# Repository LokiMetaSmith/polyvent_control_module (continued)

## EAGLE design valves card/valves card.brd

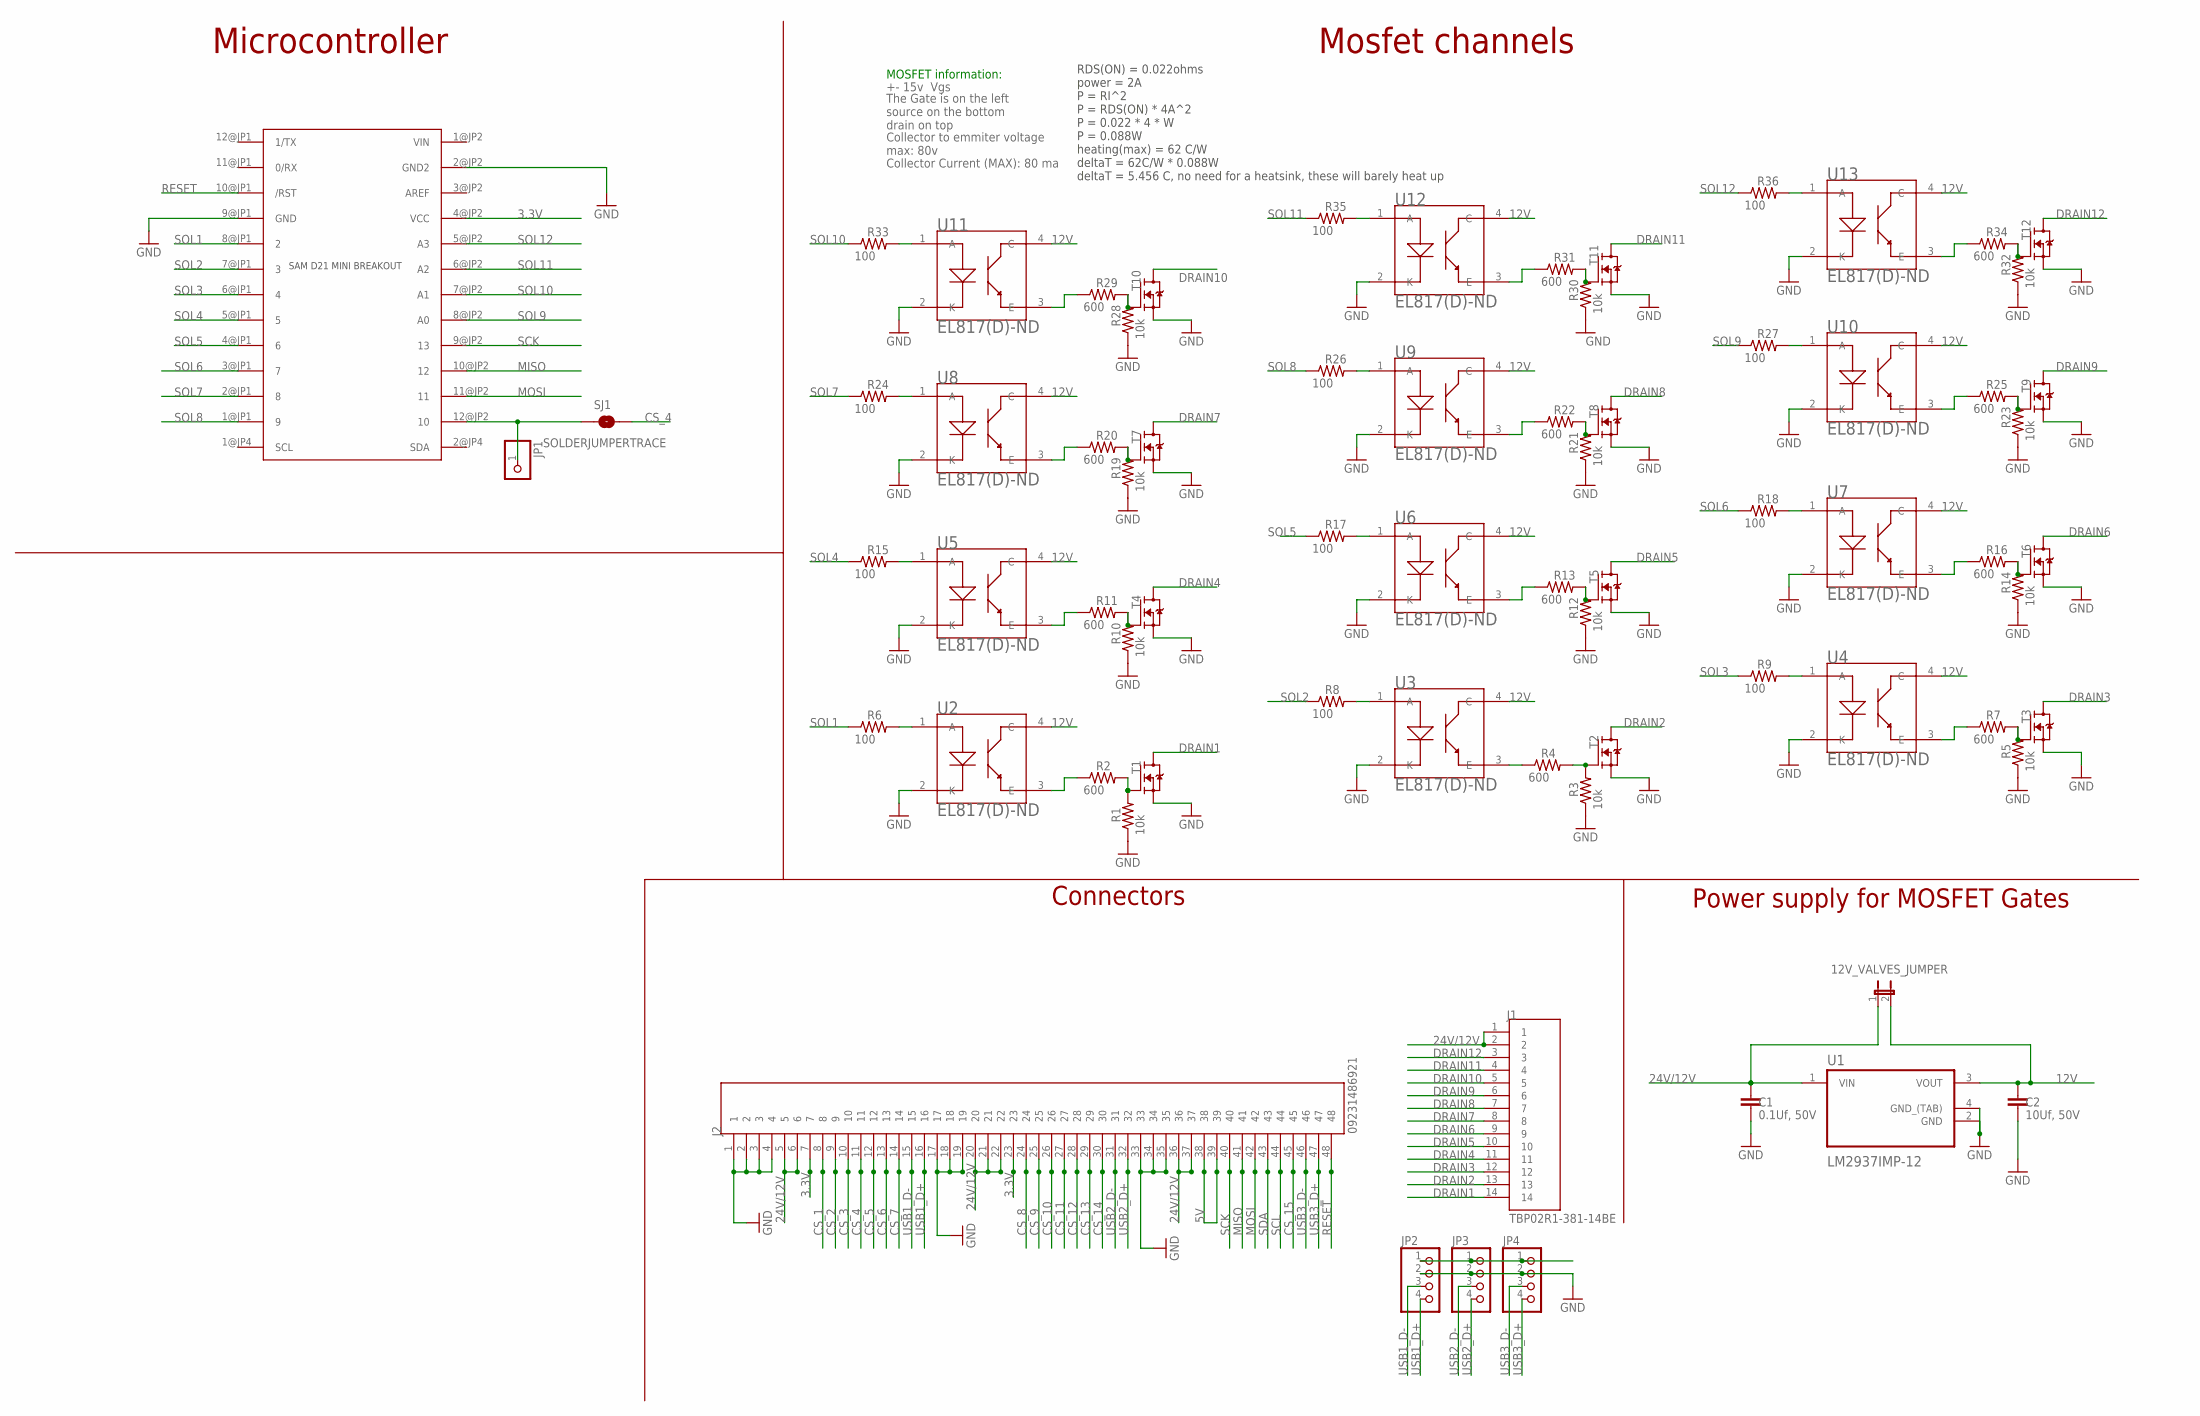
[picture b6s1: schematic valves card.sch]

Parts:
12V_VALVES_JUMPER: JUMPER-2SMD-NO; SJ_2S-NO
C1: 0.1Uf, 50V; 0805
C2: 10Uf, 50V; 0805
J1: TBP02R1-381-14BE; CUI_TBP02R1-381-14BE
J2: 09231486921; HARTING_09231486921
JP1: PINHD-1X1; 1X01
JP2, JP3, JP4: PINHD-1X4; 1X04
M2: SAM_D21_MINI_BREAKOUT; JP1_SPARKFUN-SAMD21-MINI-BREAKOUT-V10
R1, R3, R5, R10, R12, R14, R19, R21, R23, R28, R30, R32: 10k; 0805
R2, R4, R7, R11, R13, R16, R20, R22, R25, R29, R31, R34: 600; 0805
R6, R8, R9, R15, R17, R18, R24, R26, R27, R33, R35, R36: 100; 0805
SJ1: SOLDERJUMPERTRACE; SJ_2S-TRACE
T1, T2, T3, T4, T5, T6, T7, T8, T9, T10, T11, T12: IRLZ44NSTRLPBF; DPAK_TO252
U1: LM2937IMP-12; SOT230P700X180-4N
U2, U3, U4, U5, U6, U7, U8, U9, U10, U11, U12, U13: EL817(D)-ND; DIP4

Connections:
3.3V: J2.7, J2.23, M2.4@JP2 (VCC)
5V: J2.38, J2.39, JP2.1, JP3.1, JP4.1
12V: 12V_VALVES_JUMPER.2, C2.1, U1.3 (VOUT), U2.4 (C), U3.4 (C), U4.4 (C), U5.4 (C), U6.4 (C), U7.4 (C), U8.4 (C), U9.4 (C), U10.4 (C), U11.4 (C), U12.4 (C), U13.4 (C)
24V/12V: 12V_VALVES_JUMPER.1, C1.1, J1.1, J1.2, J2.5, J2.6, J2.20, J2.21, J2.22, J2.36, J2.37, U1.1 (VIN)
AREF: M2.3@JP2 (AREF)
CS_1: J2.8
CS_2: J2.9
CS_3: J2.10
CS_4: J2.11, SJ1.2
CS_5: J2.12
CS_6: J2.13
CS_7: J2.14
CS_8: J2.24
CS_9: J2.25
CS_10: J2.26
CS_11: J2.27
CS_12: J2.28
CS_13: J2.29
CS_14: J2.30
CS_15: J2.45
DRAIN1: J1.14, T1.2 (D)
DRAIN2: J1.13, T2.2 (D)
DRAIN3: J1.12, T3.2 (D)
DRAIN4: J1.11, T4.2 (D)
DRAIN5: J1.10, T5.2 (D)
DRAIN6: J1.9, T6.2 (D)
DRAIN7: J1.8, T7.2 (D)
DRAIN8: J1.7, T8.2 (D)
DRAIN9: J1.6, T9.2 (D)
DRAIN10: J1.5, T10.2 (D)
DRAIN11: J1.4, T11.2 (D)
DRAIN12: J1.3, T12.2 (D)
GND: C1.2, C2.2, J2.1, J2.2, J2.3, J2.4, J2.17, J2.18, J2.19, J2.33, J2.34, J2.35, JP2.2, JP3.2, JP4.2, M2.2@JP2 (GND2), M2.9@JP1 (GND), R1.1, R3.1, R5.1, R10.1, R12.1, R14.1, R19.1, R21.1, R23.1, R28.1, R30.1, R32.1, T1.3 (S), T2.3 (S), T3.3 (S), T4.3 (S), T5.3 (S), T6.3 (S), T7.3 (S), T8.3 (S), T9.3 (S), T10.3 (S), T11.3 (S), T12.3 (S), U1.2 (GND), U1.4 (GND_(TAB)), U2.2 (K), U3.2 (K), U4.2 (K), U5.2 (K), U6.2 (K), U7.2 (K), U8.2 (K), U9.2 (K), U10.2 (K), U11.2 (K), U12.2 (K), U13.2 (K)
MISO: J2.41, M2.10@JP2 (12)
MOSI: J2.42, M2.11@JP2 (11)
unnamed: JP1.1, M2.12@JP2 (10), SJ1.1
unnamed: R6.2, U2.1 (A)
unnamed: R1.2, R2.2, T1.1 (G)
unnamed: R2.1, U2.3 (E)
unnamed: R3.2, R4.2, T2.1 (G)
unnamed: R4.1, U3.3 (E)
unnamed: R8.2, U3.1 (A)
unnamed: R5.2, R7.2, T3.1 (G)
unnamed: R7.1, U4.3 (E)
unnamed: R9.2, U4.1 (A)
unnamed: R10.2, R11.2, T4.1 (G)
unnamed: R11.1, U5.3 (E)
unnamed: R15.2, U5.1 (A)
unnamed: R12.2, R13.2, T5.1 (G)
unnamed: R13.1, U6.3 (E)
unnamed: R17.2, U6.1 (A)
unnamed: R14.2, R16.2, T6.1 (G)
unnamed: R16.1, U7.3 (E)
unnamed: R18.2, U7.1 (A)
unnamed: R19.2, R20.2, T7.1 (G)
unnamed: R20.1, U8.3 (E)
unnamed: R24.2, U8.1 (A)
unnamed: R21.2, R22.2, T8.1 (G)
unnamed: R22.1, U9.3 (E)
unnamed: R26.2, U9.1 (A)
unnamed: R23.2, R25.2, T9.1 (G)
unnamed: R25.1, U10.3 (E)
unnamed: R27.2, U10.1 (A)
unnamed: R28.2, R29.2, T10.1 (G)
unnamed: R29.1, U11.3 (E)
unnamed: R33.2, U11.1 (A)
unnamed: R30.2, R31.2, T11.1 (G)
unnamed: R31.1, U12.3 (E)
unnamed: R35.2, U12.1 (A)
unnamed: R32.2, R34.2, T12.1 (G)
unnamed: R34.1, U13.3 (E)
unnamed: R36.2, U13.1 (A)
RESET: J2.48, M2.10@JP1 (/RST)
SCK: J2.40, M2.9@JP2 (13)
SCL: J2.44
SDA: J2.43
SOL1: M2.8@JP1 (2), R6.1
SOL2: M2.7@JP1 (3), R8.1
SOL3: M2.6@JP1 (4), R9.1
SOL4: M2.5@JP1 (5), R15.1
SOL5: M2.4@JP1 (6), R17.1
SOL6: M2.3@JP1 (7), R18.1
SOL7: M2.2@JP1 (8), R24.1
SOL8: M2.1@JP1 (9), R26.1
SOL9: M2.8@JP2 (A0), R27.1
SOL10: M2.7@JP2 (A1), R33.1
SOL11: M2.6@JP2 (A2), R35.1
SOL12: M2.5@JP2 (A3), R36.1
USB1_D+: J2.16, JP2.4
USB1_D-: J2.15, JP2.3
USB2_D+: J2.32, JP3.4
USB2_D-: J2.31, JP3.3
USB3_D+: J2.47, JP4.4
USB3_D-: J2.46, JP4.3
VIN: M2.1@JP2 (VIN)

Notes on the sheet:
The Gate is on the left source on the bottom drain on top
+- 15v Vgs
Collector to emmiter voltage max: 80v
Collector Current (MAX): 80 ma
MOSFET information:
RDS(ON) = 0.022ohms power = 2A P = RI^2 P = RDS(ON) * 4A^2 P = 0.022 * 4 * W P = 0.088W heating(max) = 62 C/W deltaT = 62C/W * 0.088W deltaT = 5.456 C, no need for a heatsink, these will barely heat up
Mosfet channels
Power supply for MOSFET Gates
Microcontroller
Connectors

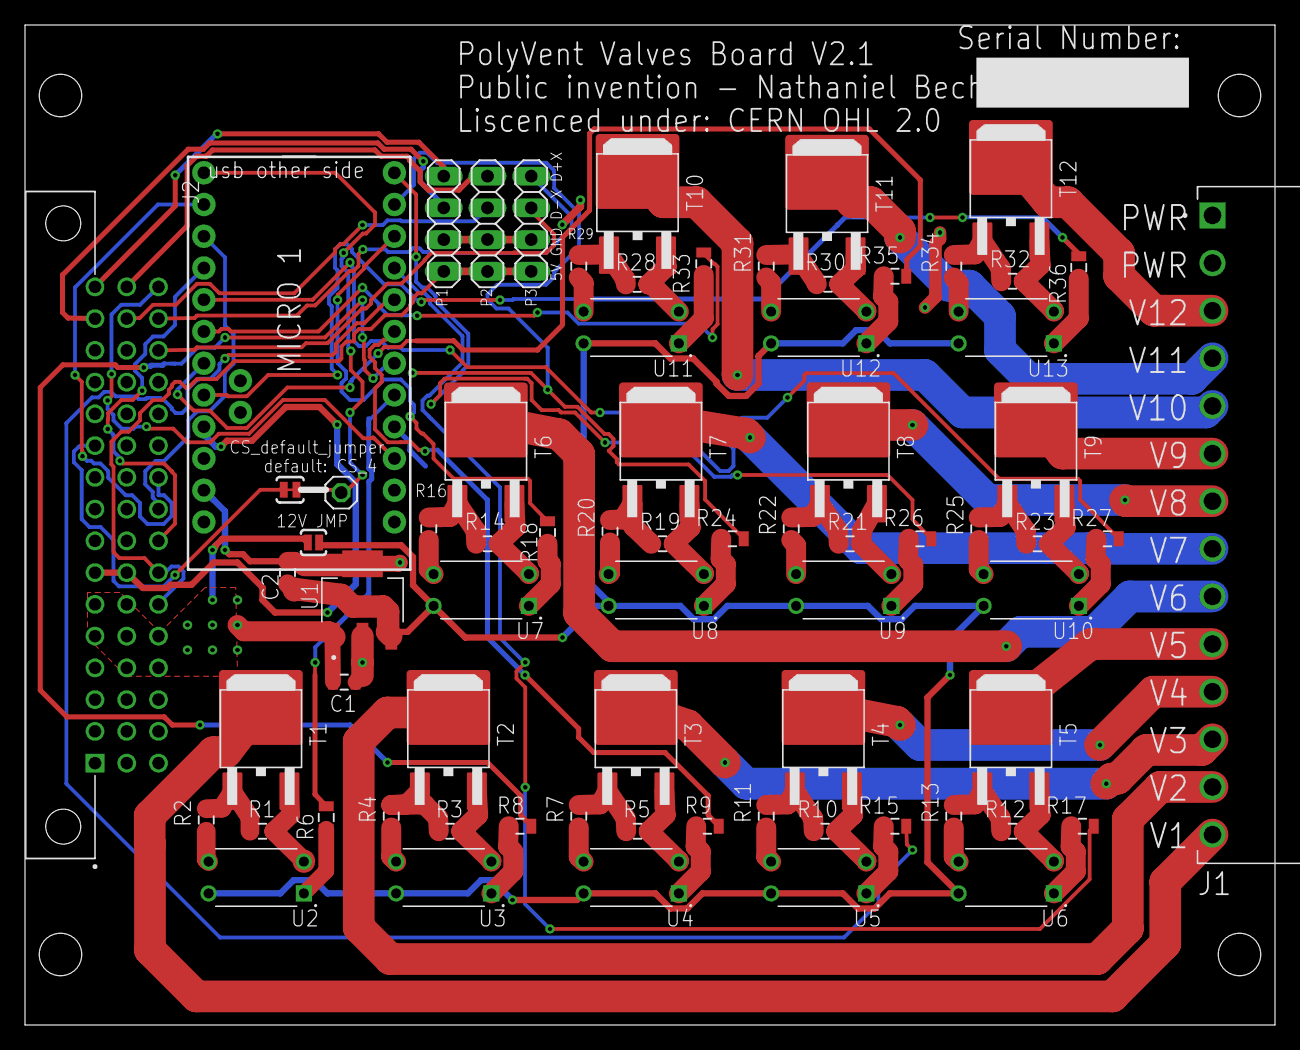
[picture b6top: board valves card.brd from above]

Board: 2 copper layers, 100.0 x 80.0 mm, 72 parts (0 on the bottom side), 77 nets.

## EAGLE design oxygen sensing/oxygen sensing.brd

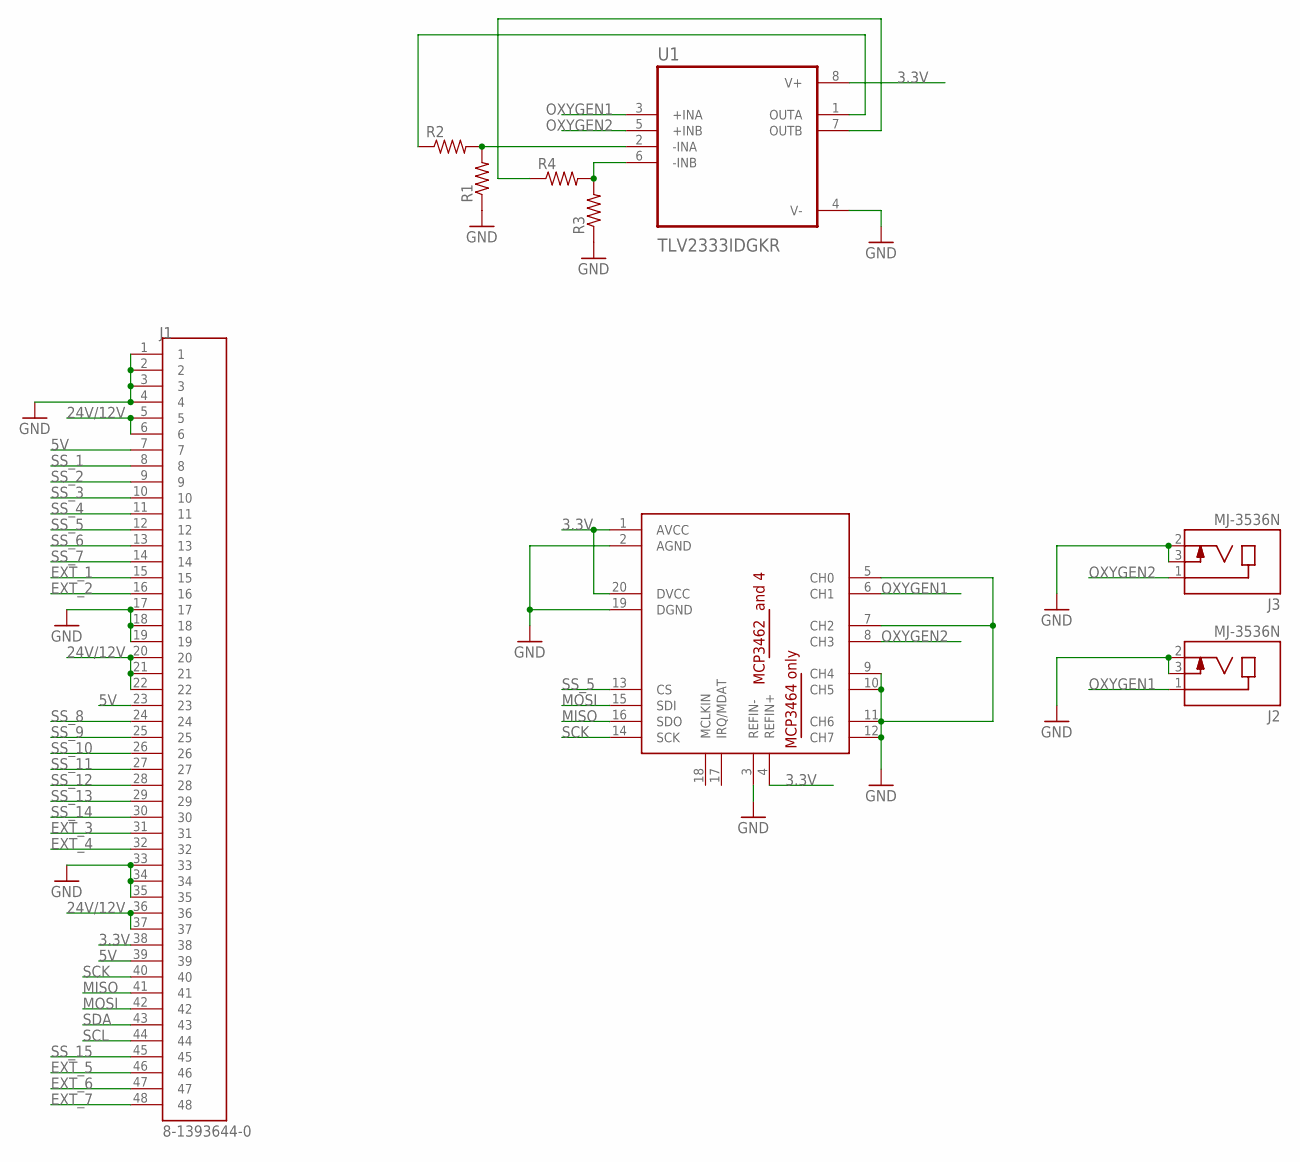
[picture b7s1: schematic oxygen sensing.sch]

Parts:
J1: 8-1393644-0; TE_8-1393644-0
J2, J3: MJ-3536N; CUI_MJ-3536N
R1, R2, R3, R4: RESISTOR0805-RES; 0805
U1: TLV2333IDGKR; SOP65P490X110-8N
U$1: MCP346X-E/ST; TSSOP20

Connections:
3.3V: J1.38, U1.8 (V+), U$1.1 (AVCC), U$1.4 (REFIN+), U$1.20 (DVCC)
5V: J1.7, J1.23, J1.39
24V/12V: J1.5, J1.6, J1.20, J1.21, J1.22, J1.36, J1.37
EXT_1: J1.15
EXT_2: J1.16
EXT_3: J1.31
EXT_4: J1.32
EXT_5: J1.46
EXT_6: J1.47
EXT_7: J1.48
GND: J1.1, J1.2, J1.3, J1.4, J1.17, J1.18, J1.19, J1.33, J1.34, J1.35, J2.2, J2.3, J3.2, J3.3, R1.1, R3.1, U1.4 (V-), U$1.2 (AGND), U$1.3 (REFIN-), U$1.5 (CH0), U$1.7 (CH2), U$1.9 (CH4), U$1.10 (CH5), U$1.11 (CH6), U$1.12 (CH7), U$1.19 (DGND)
MISO: J1.41, U$1.16 (SDO)
MOSI: J1.42, U$1.15 (SDI)
unnamed: R1.2, R2.2, U1.2 (-INA)
unnamed: R3.2, R4.2, U1.6 (-INB)
unnamed: R2.1, U1.1 (OUTA)
unnamed: R4.1, U1.7 (OUTB)
OXYGEN1: J2.1, U1.3 (+INA), U$1.6 (CH1)
OXYGEN2: J3.1, U1.5 (+INB), U$1.8 (CH3)
SCK: J1.40, U$1.14 (SCK)
SCL: J1.44
SDA: J1.43
SS_1: J1.8
SS_2: J1.9
SS_3: J1.10
SS_4: J1.11
SS_5: J1.12, U$1.13 (CS)
SS_6: J1.13
SS_7: J1.14
SS_8: J1.24
SS_9: J1.25
SS_10: J1.26
SS_11: J1.27
SS_12: J1.28
SS_13: J1.29
SS_14: J1.30
SS_15: J1.45

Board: 2 copper layers, 9 parts (0 on the bottom side), 14 nets, no tracks yet.

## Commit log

2021-07-04 added folder structure
2021-07-10 Add new directory
2021-07-10 Upload New File
2021-07-12 Deleted 1.Idea/Active/Archive/.gitkeep
2021-07-12 Add new file
2021-07-12 Update Idea->design_checklist
2021-07-14 Update 1.Idea/Accepted/Modular_Electronics_V0.2/idea explanation.txt Deleted 1.Idea/Active/001_Modular_electronics_more_manufacturable_(V2)/.gitkeep, 1.Idea/Active/001_Modular_electronics_more_manufa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
2021-07-15 added idea diagram
2021-08-05 Deleted 1.Idea/Accepted/.gitkeep, 1.Idea/Active/001_Modular_electronics_more_manufacturable_(V2)/.gitkeep, 1.Idea/Active/001_Modular_electronics_more_manufacturable_(V2)/Idea description, 1.Idea/Acti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
2021-09-05 added the backplane, created a blank card
2021-09-07 routed the wires between backplane connectors, and alligned them with the centers
2021-09-07 finished backplane
2021-09-08 added libraries and started work on the motor control card
2021-09-08 finished motor board, will test it on a breadboard now to see if everything makes sense
2021-09-09 motor driver schematic has been verified, added the valves board, will validate it though
2021-09-09 worked on the perfboard prototype card, validated the valves board mechanism
2021-09-11 general update of most things
2021-09-13 started bom creation
2021-09-13 cleanup
2021-09-13 cleanup so I can go into a past branch
2021-09-13 fixed library attributes for the din41612 connector, fixed git problems
2021-09-13 added cam data
2021-09-16 added cam data, and ordered pcb's based on that cam data, will clean up repo next
2021-09-23 added libraries
2021-09-30 added liscences
2021-09-30 cleaned up the folder
2021-10-08 saved changes
2021-10-12 modified backplane
2021-10-12 modified backplane and added new files
2021-10-13 changes saved before switching branch
2021-10-13 commiting to switch branch
2021-10-13 removed ds stores
2021-10-13 added labeled backplane breakout connector, backplane pcb is done
2021-10-14 tri poloski
2021-10-14 fixed SAMD21 library
2021-10-14 fixed up SAMD21 library, should not be giving us any problems anymore
2021-10-14 fixed stepper driver library
2021-10-14 updated libraries in the boards, traces broke (to be be expected)
2021-10-14 re routed broken connections from last commit, parts should work now
2021-10-14 cleaned up valves board silkscreen, moved header forwards
2021-10-14 improved silkscreen for valve board
2021-10-14 cleaned up sensor board silkscreen + added test pads
2021-10-14 added folder for new esp32 card
2021-10-15 changed pinouts for the boards, next I have to make accomodations for new pinouts and the USB selector system
2021-10-15 added a library for the switch I'll be using, and I updated the backplane pinout
2021-10-16 made card holes bigger, started usb port work, but I'm not done that part yet
2021-10-16 USB system mods complete on the main board, valves board, and motor board
2021-10-16 added on light to main card
2021-10-16 did some small correction work on the boards
2021-10-16 cleaned up the repo, removed old eagle saves (they're still in the design history, and I removed the old cam data, that has to be redone for the new revisions
2021-10-16 finished cleanup started review and final mods
2021-10-16 final mods to the boards, next commit will add the CAM data, it will be the final commit before the polyvent V2.1 design merge, and I'm ready to order boards
2021-10-17 final commit before merge, generated cam data
2021-10-21 created backplane V1.2, which can take more power, and has a label to specify wether it is 1oz or 2oz copper
2021-10-21 cleaned backplane folder
2021-10-21 added even wider traces to the backplane
2021-10-21 added overall schematic of the device
2021-10-22 worked on the polyvent symbols library
2021-10-22 added schematics for the overall system
2021-10-22 got rid of a 0.05mm offset in the position of the din41612 connectors
2021-11-01 added pdf versions of the schematics
2021-11-19 small mechanical changes to some cards, output connectors were moved around
2021-11-19 fixed swithc pinout on the main board
2021-11-20 added sparkfun level shifter to breakout to the sensing board
2021-11-22 update before adc change
2021-11-23 added the new oxygen sensing system to the control module
2021-11-24 updated libraries to generate better bom's
2021-11-24 finished V2.2 control module update
2021-11-24 fixed small issue with the sensor emf shield:
2021-11-24 small fixes
2022-01-12 added version 2.2 of the main board, which fixes the I2C pin problem
2022-01-12 added case cad's
2022-01-12 added names, and added a blank card faceplate
2022-01-12 added diode for proportional valve
2022-01-22 merged the firmware from the firmware repo with this one, and changed the folder structure
2022-07-15 fixed the emi cap footprint on the sensing card
2022-07-15 fixed problems with control module 2.2, all boards are now ready to order
2022-07-15 added loose ends to last update
2022-10-12 master branch ready for RICE university
